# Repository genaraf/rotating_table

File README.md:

b# Rotating Table (ESP-IDF, M5Stamp-C3)

Проект управления вращающимся столом с наклоном:
- шаговый двигатель 28BYJ-48 через ULN2003
- серво для наклона (PWM)
- кнопка на `GPIO10`: короткое нажатие `Power`, удержание > 5 сек `Reset`
- Web UI для настроек Wi-Fi, движения и профилей

## Реализовано
- Wi-Fi:
  - `STA + fallback AP` (если STA не поднялся, включается AP)
  - `AP only`
- Web UI:
  - вкладка `Control`: профиль, угол поворота, угол наклона, `Start/Stop`, `Reset(Home 0/0)`
  - вкладка `Profiles`: параметры и профили `create / copy / delete / activate`
  - вкладка `Wi-Fi`: режим AP/STA и SSID/пароли
  - вкладка `About`: имя, версия, `Reset settings` с подтверждением
- Сохранение настроек в NVS

Параметры по умолчанию:
- `min_angle = -45`
- `max_angle = 45`
- стартовый угол при загрузке: `0`
- `turn_grad = 10` означает: 1 оборот стола изменяет наклон на 10 градусов

## Структура модулей
- `main/main.c` — оркестрация запуска
- `main/app_state.c` — состояние, профили, load/save NVS
- `main/motor_control.c` — шаговик + серво + motion task
- `main/button_control.c` — обработка кнопок
- `main/wifi_manager.c` — STA/AP/fallback
- `main/web_server.c` — Web UI и REST API
- `main/board_config.h` — пины и калибровка моторов

## Пины и калибровка (пункт 3)
Все аппаратные параметры вынесены в `main/board_config.h`:
- GPIO пины для ULN2003, серво и кнопок
- `STEPPER_STEPS_PER_REV`
- `STEPPER_DIR` (`1` или `-1`)
- `SERVO_MIN_US`, `SERVO_MAX_US`, `SERVO_PERIOD_HZ`
- пределы наклона `TILT_MIN_DEG_LIMIT`, `TILT_MAX_DEG_LIMIT`

Текущая дефолтная карта:
- `IN1=GPIO4`, `IN2=GPIO5`, `IN3=GPIO6`, `IN4=GPIO7`
- `SERVO_PWM=GPIO8`
- `BTN_POWER=GPIO10`, `BTN_RESET=GPIO10` (одна кнопка: short/long press)

Если у вас другая разводка, меняйте только `board_config.h`.

## Схема подключения
PNG версия: `docs/wiring-diagram.png`

```text
M5Stamp-C3                     ULN2003 board                 28BYJ-48
-----------                    -------------                 --------
GPIO4  ----------------------> IN1
GPIO5  ----------------------> IN2
GPIO6  ----------------------> IN3
GPIO7  ----------------------> IN4
GND    ----------------------> GND -------------------------> GND
5V ext ----------------------> VCC -------------------------> +5V motor
                                                     (5-pin cable from ULN2003 to motor)

M5Stamp-C3                     Servo (tilt)
-----------                    ------------
GPIO8  ----------------------> PWM/SIG
GND    ----------------------> GND
5V ext ----------------------> +5V

Button (active-low, shared actions):
GPIO10 ---[button]---------- GND
short press -> power ON/OFF
hold >5 sec -> factory reset

Power:
- M5Stamp-C3: from USB/5V as usual
- ULN2003 + stepper: external 5V
- Servo: external 5V (желательно отдельная линия)
- All grounds must be common: M5 GND = ULN2003 GND = Servo GND = PSU GND
```

Генератор PNG: `tools/generate_wiring_png.py`

## Сборка и прошивка
```bash
idf.py set-target esp32c3
idf.py build
idf.py -p /dev/ttyUSB0 flash monitor
```

## Web UI
- STA режим: откройте IP устройства в локальной сети
- AP режим: подключитесь к `RTable-Setup` (пароль `12345678`) и откройте `http://192.168.4.1/`

## Подключение питания
- ULN2003 + 28BYJ-48: 5V
- Серво: отдельный 5V источник (желательно)
- Обязателен общий GND между M5Stamp-C3, ULN2003 и серво

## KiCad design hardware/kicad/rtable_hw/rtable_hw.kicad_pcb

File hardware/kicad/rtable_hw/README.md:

щл# rtable_hw (KiCad)

Files:
- `rtable_hw.kicad_pro` - KiCad project file
- `rtable_hw.kicad_sch` - full wiring schematic with symbols and nets

Open:
1. Start KiCad
2. Open `rtable_hw.kicad_pro`
3. Open schematic editor and load `rtable_hw.kicad_sch`

Implemented schematic blocks:
- `J1` M5Stamp-C3 header
- `U1` ULN2003A
- `J2` 28BYJ-48 motor connector
- `J3` Servo connector
- `J4` Button connector
- `J5` +5V input connector

Implemented net mapping:
- GPIO4/5/6/7 -> ULN2003 IN1/IN2/IN3/IN4
- ULN2003 O1/O2/O3/O4 -> motor coils `COIL_A/B/C/D`
- ULN2003 `COM` -> `+5V`, ULN2003 `GND` -> `GND`
- GPIO8 -> Servo signal
- GPIO10 -> Button (active-low)
- External 5V for ULN2003 + Servo
- Common GND across all blocks

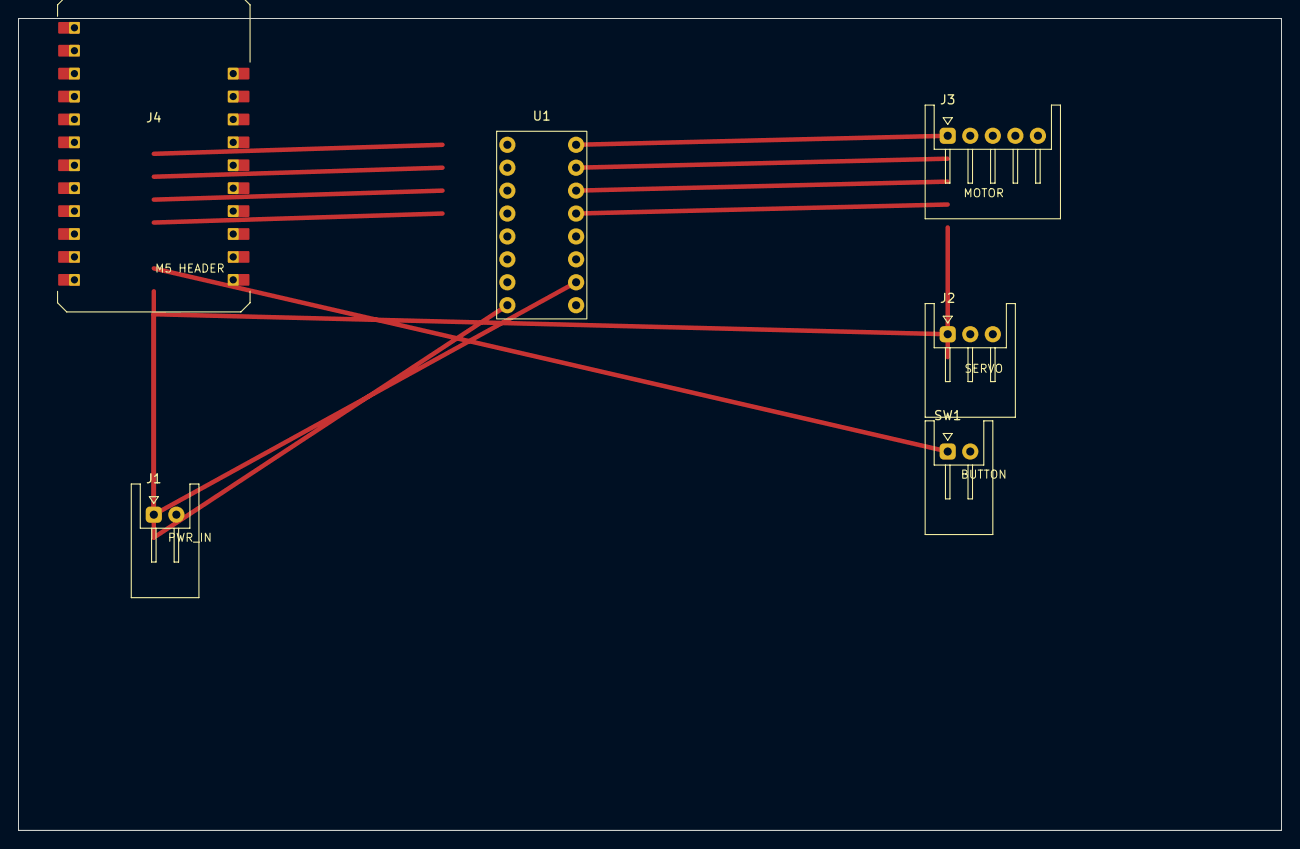
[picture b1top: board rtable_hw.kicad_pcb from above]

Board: 2 copper layers, 140.0 x 90.0 mm, 6 parts (0 on the bottom side), 12 nets.

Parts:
J1: PWR_IN; S02B-XASS-1
J2: SERVO; S03B-XASK-1
J3: MOTOR; S05B-XASK-1
J4: M5 HEADER; M5STAMP-C3C3U
SW1: BUTTON; S02B-XASS-1
U1: ULN2003A; ULN2003_DIP16

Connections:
+5V: J1.1, J2.2, J3.5, J4.8, U1.9
COIL_A: J3.1, U1.16
COIL_B: J3.2, U1.15
COIL_C: J3.3, U1.14
COIL_D: J3.4, U1.13
GND: J1.2, J2.3, J4.7, SW1.2, U1.8
GPIO4: J4.1, U1.1
GPIO5: J4.2, U1.2
GPIO6: J4.3, U1.3
GPIO7: J4.4, U1.4
GPIO8: J2.1, J4.5
GPIO10: J4.6, SW1.1

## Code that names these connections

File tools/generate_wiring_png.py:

#!/usr/bin/env python3
import struct
import zlib

W, H = 1600, 1000

WHITE = (250, 252, 255)
BLACK = (20, 30, 35)
GRAY = (110, 125, 135)
BLUE = (36, 99, 161)
GREEN = (34, 139, 88)
ORANGE = (214, 137, 16)
RED = (180, 48, 48)
PURPLE = (120, 70, 170)
BOX_BG = (238, 244, 248)

img = [[WHITE for _ in range(W)] for _ in range(H)]

FONT = {
    'A':[0x0E,0x11,0x11,0x1F,0x11,0x11,0x11],'B':[0x1E,0x11,0x11,0x1E,0x11,0x11,0x1E],
    'C':[0x0E,0x11,0x10,0x10,0x10,0x11,0x0E],'D':[0x1E,0x11,0x11,0x11,0x11,0x11,0x1E],
    'E':[0x1F,0x10,0x10,0x1E,0x10,0x10,0x1F],'F':[0x1F,0x10,0x10,0x1E,0x10,0x10,0x10],
    'G':[0x0E,0x11,0x10,0x17,0x11,0x11,0x0E],'H':[0x11,0x11,0x11,0x1F,0x11,0x11,0x11],
    'I':[0x1F,0x04,0x04,0x04,0x04,0x04,0x1F],'J':[0x07,0x02,0x02,0x02,0x12,0x12,0x0C],
    'K':[0x11,0x12,0x14,0x18,0x14,0x12,0x11],'L':[0x10,0x10,0x10,0x10,0x10,0x10,0x1F],
    'M':[0x11,0x1B,0x15,0x15,0x11,0x11,0x11],'N':[0x11,0x19,0x15,0x13,0x11,0x11,0x11],
    'O':[0x0E,0x11,0x11,0x11,0x11,0x11,0x0E],'P':[0x1E,0x11,0x11,0x1E,0x10,0x10,0x10],
    'Q':[0x0E,0x11,0x11,0x11,0x15,0x12,0x0D],'R':[0x1E,0x11,0x11,0x1E,0x14,0x12,0x11],
    'S':[0x0F,0x10,0x10,0x0E,0x01,0x01,0x1E],'T':[0x1F,0x04,0x04,0x04,0x04,0x04,0x04],
    'U':[0x11,0x11,0x11,0x11,0x11,0x11,0x0E],'V':[0x11,0x11,0x11,0x11,0x11,0x0A,0x04],
    'W':[0x11,0x11,0x11,0x15,0x15,0x15,0x0A],'X':[0x11,0x11,0x0A,0x04,0x0A,0x11,0x11],
    'Y':[0x11,0x11,0x0A,0x04,0x04,0x04,0x04],'Z':[0x1F,0x01,0x02,0x04,0x08,0x10,0x1F],
    '0':[0x0E,0x11,0x13,0x15,0x19,0x11,0x0E],'1':[0x04,0x0C,0x04,0x04,0x04,0x04,0x0E],
    '2':[0x0E,0x11,0x01,0x02,0x04,0x08,0x1F],'3':[0x1E,0x01,0x01,0x0E,0x01,0x01,0x1E],
    '4':[0x02,0x06,0x0A,0x12,0x1F,0x02,0x02],'5':[0x1F,0x10,0x10,0x1E,0x01,0x01,0x1E],
    '6':[0x0E,0x10,0x10,0x1E,0x11,0x11,0x0E],'7':[0x1F,0x01,0x02,0x04,0x08,0x08,0x08],
    '8':[0x0E,0x11,0x11,0x0E,0x11,0x11,0x0E],'9':[0x0E,0x11,0x11,0x0F,0x01,0x01,0x0E],
    '-':[0x00,0x00,0x00,0x1F,0x00,0x00,0x00],'>':[0x00,0x10,0x08,0x04,0x08,0x10,0x00],
    '+':[0x00,0x04,0x04,0x1F,0x04,0x04,0x00],'/':[0x01,0x02,0x04,0x08,0x10,0x00,0x00],
    '(':[0x02,0x04,0x08,0x08,0x08,0x04,0x02],')':[0x08,0x04,0x02,0x02,0x02,0x04,0x08],
    '.':[0x00,0x00,0x00,0x00,0x00,0x06,0x06],':':[0x00,0x06,0x06,0x00,0x06,0x06,0x00],
    '=':[0x00,0x1F,0x00,0x1F,0x00,0x00,0x00],' ':[0x00,0x00,0x00,0x00,0x00,0x00,0x00],
}


def put(x, y, c):
    if 0 <= x < W and 0 <= y < H:
        img[y][x] = c


def fill_rect(x, y, w, h, c):
    for yy in range(y, y + h):
        if 0 <= yy < H:
            row = img[yy]
            x1 = max(0, x)
            x2 = min(W, x + w)
            for xx in range(x1, x2):
                row[xx] = c


def rect(x, y, w, h, c, t=2):
    fill_rect(x, y, w, t, c)
    fill_rect(x, y + h - t, w, t, c)
    fill_rect(x, y, t, h, c)
    fill_rect(x + w - t, y, t, h, c)


def line(x1, y1, x2, y2, c, thick=2):
    dx = abs(x2 - x1)
    dy = abs(y2 - y1)
    sx = 1 if x1 < x2 else -1
    sy = 1 if y1 < y2 else -1
    err = dx - dy
    while True:
        for ty in range(-thick // 2, thick // 2 + 1):
            for tx in range(-thick // 2, thick // 2 + 1):
                put(x1 + tx, y1 + ty, c)
        if x1 == x2 and y1 == y2:
            break
        e2 = 2 * err
        if e2 > -dy:
            err -= dy
            x1 += sx
        if e2 < dx:
            err += dx
            y1 += sy


def arrow(x1, y1, x2, y2, c, thick=3):
    line(x1, y1, x2, y2, c, thick)
    if abs(x2 - x1) >= abs(y2 - y1):
        sign = 1 if x2 > x1 else -1
        line(x2, y2, x2 - 14 * sign, y2 - 8, c, thick)
        line(x2, y2, x2 - 14 * sign, y2 + 8, c, thick)
    else:
        sign = 1 if y2 > y1 else -1
        line(x2, y2, x2 - 8, y2 - 14 * sign, c, thick)
        line(x2, y2, x2 + 8, y2 - 14 * sign, c, thick)


def text(x, y, s, c=BLACK, scale=3):
    xx = x
    for ch in s.upper():
        glyph = FONT.get(ch, FONT[' '])
        for row_idx, row_bits in enumerate(glyph):
            for bit in range(5):
                if row_bits & (1 << (4 - bit)):
                    fill_rect(xx + bit * scale, y + row_idx * scale, scale, scale, c)
        xx += 6 * scale


# Background sections
fill_rect(0, 0, W, H, WHITE)
text(360, 30, "WIRING DIAGRAM M5STAMP-C3 / ULN2003 / 28BYJ-48 / SERVO", BLACK, 4)
text(470, 72, "GPIO: 4 5 6 7 8 10", GRAY, 3)

# Device boxes
rect(80, 150, 320, 620, BLUE, 4)
fill_rect(84, 154, 312, 612, BOX_BG)
text(130, 180, "M5STAMP-C3", BLUE, 4)

rect(540, 170, 320, 420, GREEN, 4)
fill_rect(544, 174, 312, 412, BOX_BG)
text(615, 200, "ULN2003", GREEN, 4)

rect(1040, 190, 320, 220, ORANGE, 4)
fill_rect(1044, 194, 312, 212, BOX_BG)
text(1070, 220, "28BYJ-48 MOTOR", ORANGE, 4)

rect(1040, 470, 320, 190, PURPLE, 4)
fill_rect(1044, 474, 312, 182, BOX_BG)
text(1140, 500, "SERVO", PURPLE, 4)

rect(1040, 730, 320, 160, RED, 4)
fill_rect(1044, 734, 312, 152, BOX_BG)
text(1080, 760, "BUTTON (GPIO10)", RED, 3)
text(1080, 805, "SHORT: POWER", RED, 3)
text(1080, 845, "HOLD>5S: RESET", RED, 3)

# M5 pins labels
text(120, 260, "GPIO4", BLUE, 3)
text(120, 315, "GPIO5", BLUE, 3)
text(120, 370, "GPIO6", BLUE, 3)
text(120, 425, "GPIO7", BLUE, 3)
text(120, 500, "GPIO8 PWM", BLUE, 3)
text(120, 580, "GPIO10 BTN", BLUE, 3)
text(120, 660, "GND", BLUE, 3)

# ULN pins
text(590, 280, "IN1", GREEN, 3)
text(590, 335, "IN2", GREEN, 3)
text(590, 390, "IN3", GREEN, 3)
text(590, 445, "IN4", GREEN, 3)
text(590, 520, "GND", GREEN, 3)
text(710, 520, "VCC 5V", GREEN, 3)

# Connections stepper ctrl
arrow(300, 270, 580, 290, BLUE, 3)
arrow(300, 325, 580, 345, BLUE, 3)
arrow(300, 380, 580, 400, BLUE, 3)
arrow(300, 435, 580, 455, BLUE, 3)

# ULN to motor
arrow(860, 300, 1035, 300, ORANGE, 4)
text(860, 330, "5-WIRE MOTOR CABLE", ORANGE, 2)

# Servo signal
arrow(320, 510, 1035, 540, PURPLE, 3)
text(720, 545, "PWM SIGNAL", PURPLE, 2)

# Button
arrow(340, 590, 1035, 770, RED, 3)

# Ground and power rails
line(290, 670, 1400, 670, BLACK, 3)
text(670, 685, "COMMON GND", BLACK, 3)
arrow(780, 670, 780, 585, BLACK, 3)
arrow(1160, 670, 1160, 640, BLACK, 3)
arrow(700, 670, 700, 545, BLACK, 3)
arrow(1160, 670, 1160, 405, BLACK, 3)

line(480, 915, 1400, 915, ORANGE, 4)
text(760, 930, "EXTERNAL +5V", ORANGE, 3)
arrow(700, 915, 700, 560, ORANGE, 3)
arrow(1180, 915, 1180, 650, ORANGE, 3)

text(70, 915, "NOTE: ALL GROUNDS MUST BE CONNECTED TOGETHER", GRAY, 3)


def png_chunk(tag, data):
    return struct.pack("!I", len(data)) + tag + data + struct.pack("!I", zlib.crc32(tag + data) & 0xFFFFFFFF)

raw = bytearray()
for y in range(H):
    raw.append(0)
    for (r, g, b) in img[y]:
        raw.extend((r, g, b))

ihdr = struct.pack("!IIBBBBB", W, H, 8, 2, 0, 0, 0)
idat = zlib.compress(bytes(raw), 9)
out = bytearray(b"\x89PNG\r\n\x1a\n")
out += png_chunk(b"IHDR", ihdr)
out += png_chunk(b"IDAT", idat)
out += png_chunk(b"IEND", b"")

with open("/home/gena/work/Rtable/docs/wiring-diagram.png", "wb") as f:
    f.write(out)

print("written: /home/gena/work/Rtable/docs/wiring-diagram.png")
